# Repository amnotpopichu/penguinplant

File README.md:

# Project Name
project overview

# Firmware
explain it - if it exists

# CAD
go thru cad idk

# PCB
explain pcb

# Images
images go here

Demo link goes here

# Notes
Note to reviewer: Journals made before jul 10th or so will all be marked 0 hours. This is beacause I am no longer using this chip, and thus cannot claim time, and the journals are just there for my own purposes. [linked question in #forge help](https://hackclub.slack.com/archives/C0AR9KH6BU2/p1783924161370139)

# BOM

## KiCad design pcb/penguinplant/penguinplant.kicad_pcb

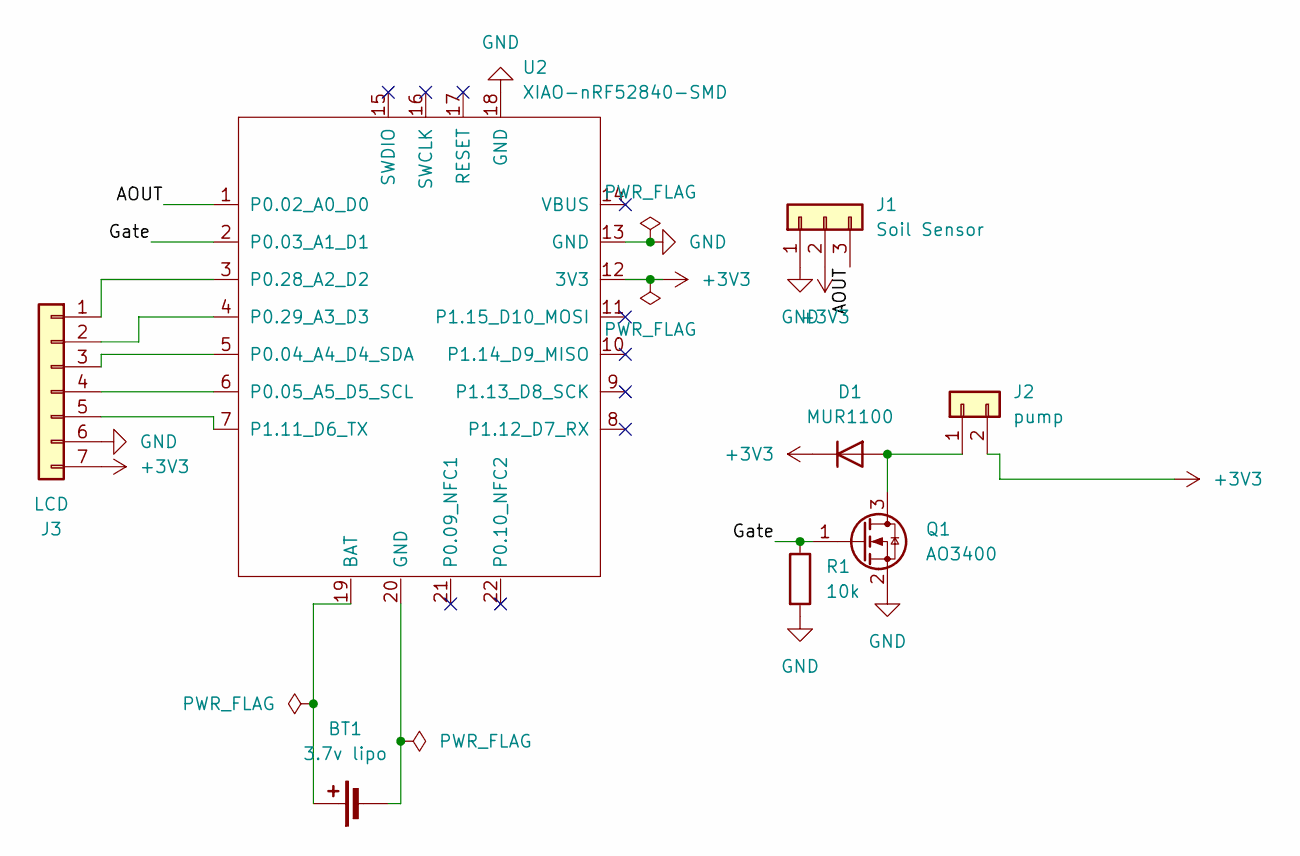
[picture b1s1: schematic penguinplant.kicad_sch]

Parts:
BT1: 3.7v lipo; PinHeader_1x02_P2.54mm_Vertical
D1: MUR1100; D_DO-41_SOD81_P10.16mm_Horizontal
J1: Soil Sensor; PinHeader_1x03_P2.54mm_Vertical
J2: pump; PinHeader_1x02_P2.54mm_Vertical
J3: LCD; PinHeader_1x07_P2.54mm_Vertical
Q1: AO3400; SOT-23
R1: 10k; R_Axial_DIN0207_L6.3mm_D2.5mm_P10.16mm_Horizontal
U2: XIAO-nRF52840-SMD

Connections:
+3V3: D1.1 (K), J1.2, J2.2, J3.7, U2.12 (3V3)
/AOUT: J1.3, U2.1 (P0.02_A0_D0)
/Gate: Q1.1 (G), R1.1, U2.2 (P0.03_A1_D1)
GND: J1.1, J3.6, Q1.2 (S), R1.2, U2.13 (GND), U2.18 (GND)
unnamed: BT1.1 (+), U2.19 (BAT)
unnamed: BT1.2 (-), U2.20 (GND)
unnamed: D1.2 (A), J2.1, Q1.3 (D)
unnamed: J3.1, U2.3 (P0.28_A2_D2)
unnamed: J3.2, U2.4 (P0.29_A3_D3)
unnamed: J3.3, U2.5 (P0.04_A4_D4_SDA)
unnamed: J3.4, U2.6 (P0.05_A5_D5_SCL)
unnamed: J3.5, U2.7 (P1.11_D6_TX)

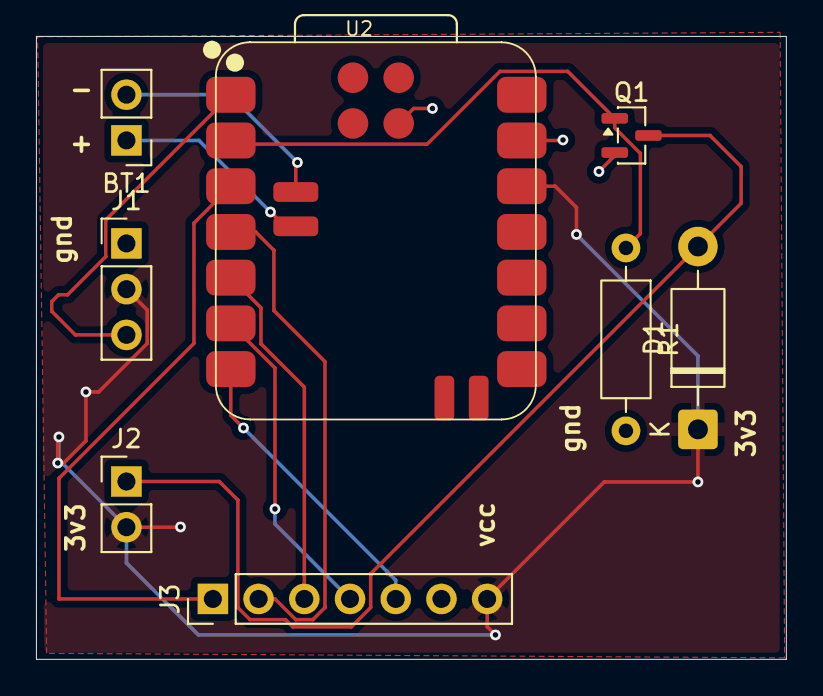
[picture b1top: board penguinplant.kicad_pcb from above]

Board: 2 copper layers, 41.7 x 34.6 mm, 8 parts (0 on the bottom side), 12 nets.

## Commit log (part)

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2026-06-09 setted up github
2026-06-09 yippie
2026-06-13 journal for today
2026-06-30 backup incase deleitng stuff goes wrong
2026-06-30 journal update
